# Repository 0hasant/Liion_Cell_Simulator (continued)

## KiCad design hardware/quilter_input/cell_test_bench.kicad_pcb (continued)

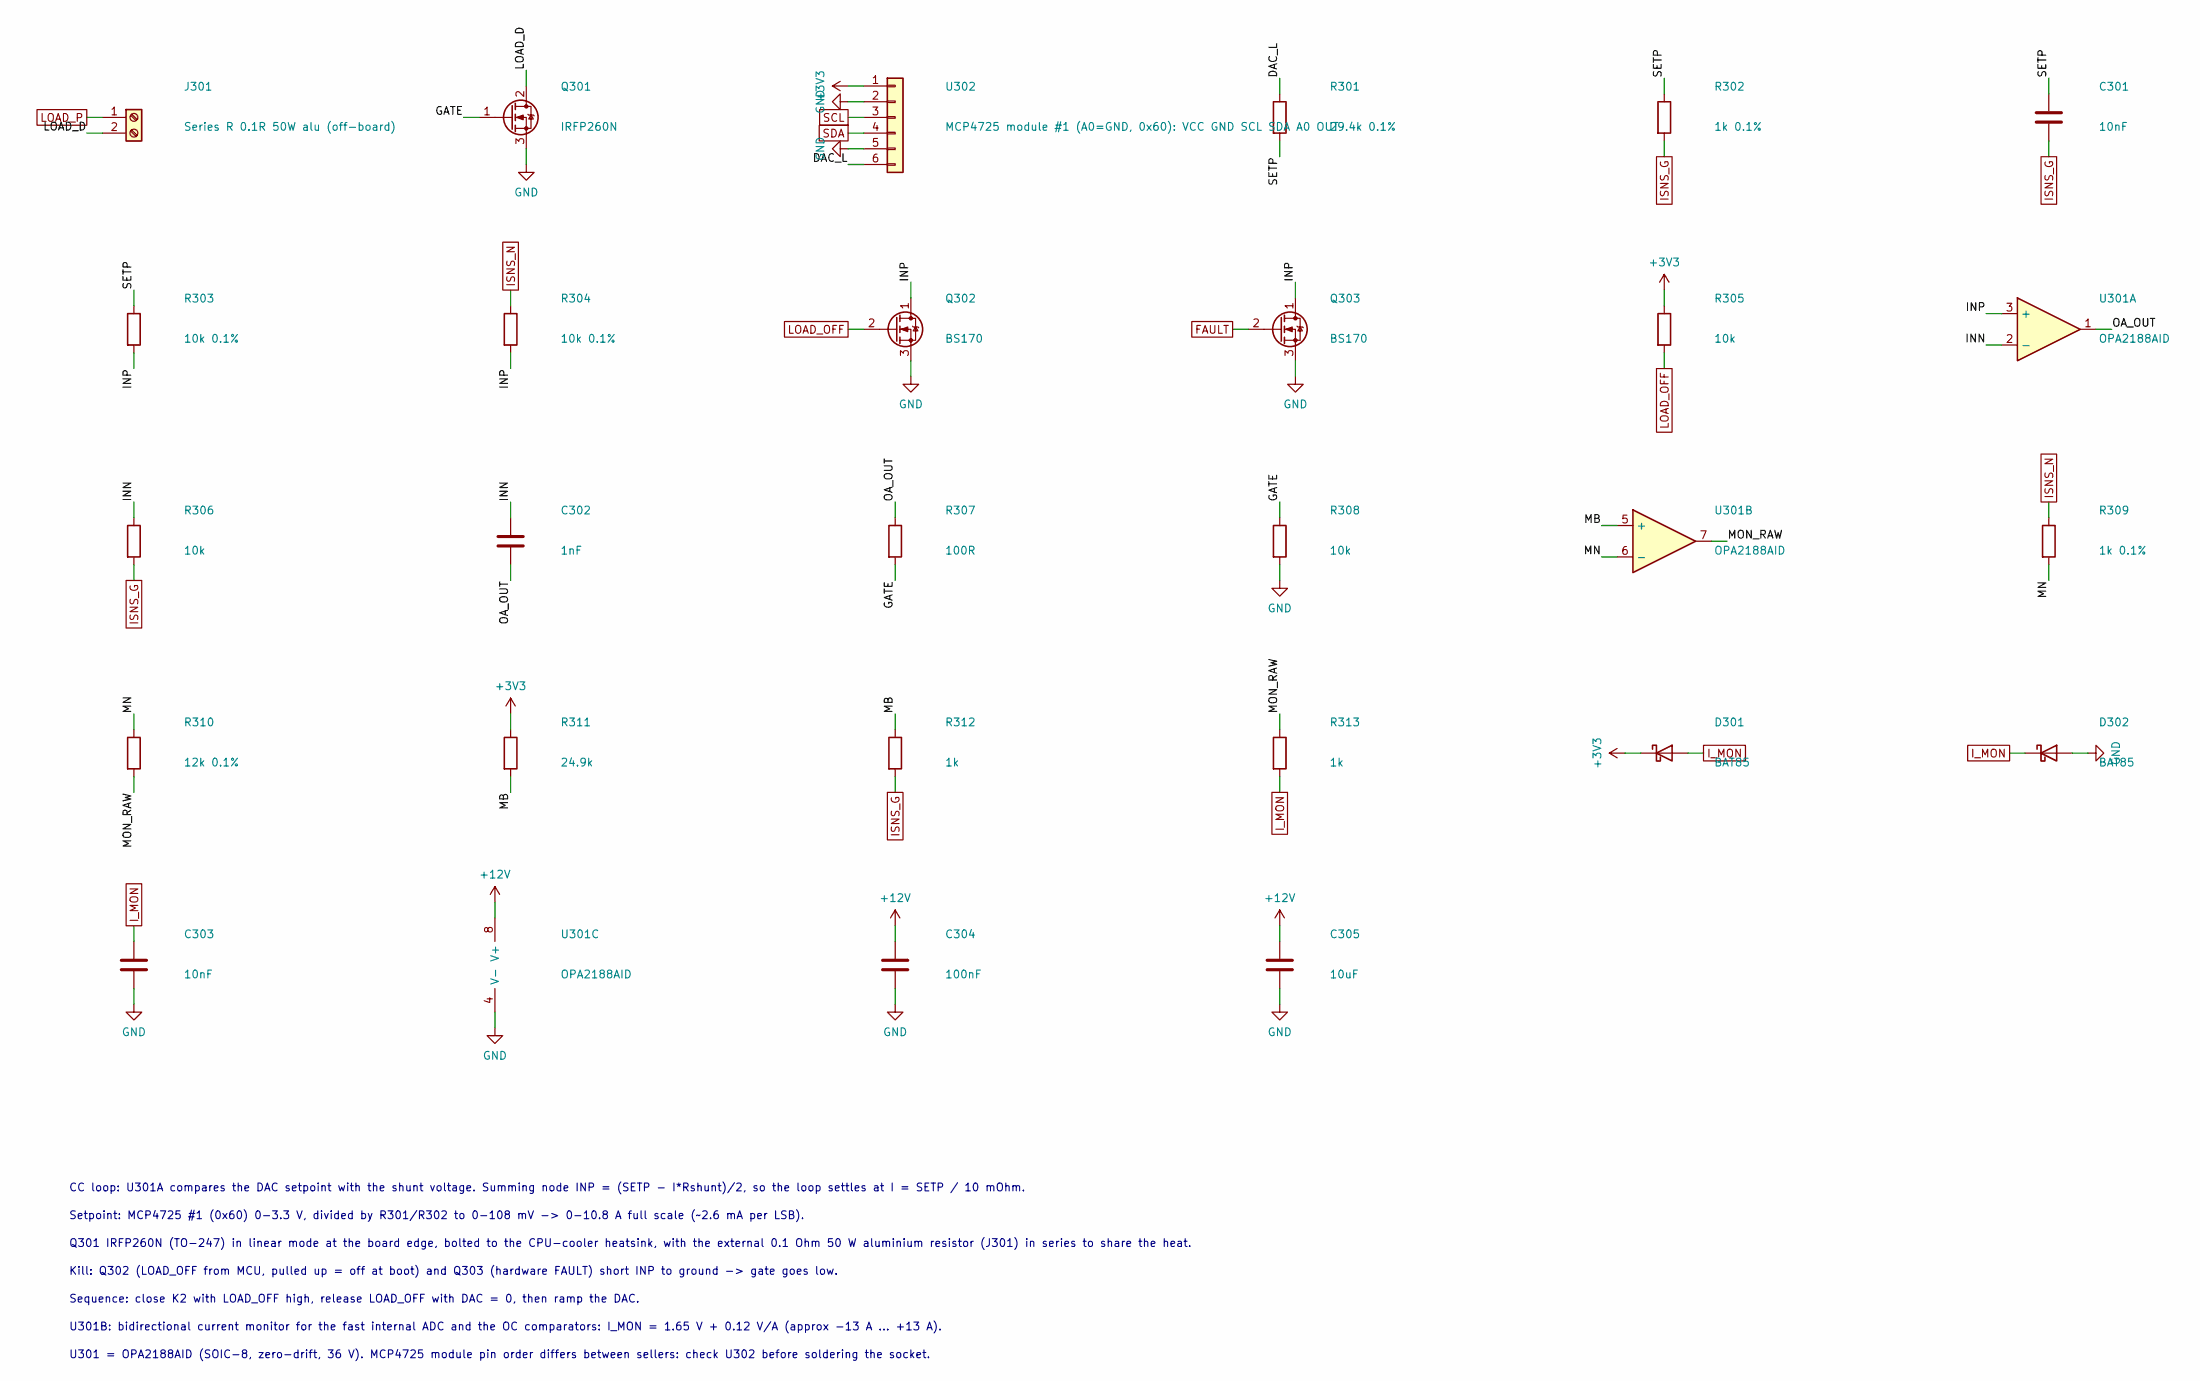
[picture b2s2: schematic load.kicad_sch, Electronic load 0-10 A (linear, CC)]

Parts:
C301, C303: 10nF; C_1206_3216Metric
C302: 1nF; C_1206_3216Metric
C304: 100nF; C_1206_3216Metric
C305: 10uF; C_1206_3216Metric
D301, D302: BAT85; D_DO-35_SOD27_P7.62mm_Horizontal; MPN BAT85,113
J301: Series R 0.1R 50W alu (off-board); TerminalBlock_Phoenix_MKDS-3-2-5.08_1x02_P5.08mm_Horizontal
Q301: IRFP260N; TO-247-3_Vertical; MPN IRFP260NPBF
Q302, Q303: BS170; TO-92_Inline_Wide; MPN BS170
R301: 29.4k 0.1%; R_1206_3216Metric
R302, R309: 1k 0.1%; R_1206_3216Metric
R303, R304: 10k 0.1%; R_1206_3216Metric
R305, R306, R308: 10k; R_1206_3216Metric
R307: 100R; R_1206_3216Metric
R310: 12k 0.1%; R_1206_3216Metric
R311: 24.9k; R_1206_3216Metric
R312, R313: 1k; R_1206_3216Metric
U301: OPA2188AID; SOIC-8_3.9x4.9mm_P1.27mm; MPN OPA2188AID
U302: MCP4725 module #1 (A0=GND, 0x60): VCC GND SCL SDA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; PinSocket_1x06_P2.54mm_Vertical

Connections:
+3V3: D301.1 (K), R305.1, R311.1, U302.1; also elsewhere on the board
+12V: C304.1, C305.1, U301.8 (V+); also elsewhere on the board
/Electronic_Load/DAC_L: R301.1, U302.6
/Electronic_Load/GATE: Q301.1 (G), R307.2, R308.1
/Electronic_Load/INN: C302.1, R306.1, U301.2 (-)
/Electronic_Load/INP: Q302.1 (D), Q303.1 (D), R303.2, R304.2, U301.3 (+)
/Electronic_Load/LOAD_D: J301.2, Q301.2 (D)
/Electronic_Load/MB: R311.2, R312.1, U301.5 (+)
/Electronic_Load/MN: R309.2, R310.1, U301.6 (-)
/Electronic_Load/MON_RAW: R310.2, R313.1, U301.7
/Electronic_Load/OA_OUT: C302.2, R307.1, U301.1
/Electronic_Load/SETP: C301.1, R301.2, R302.1, R303.1
FAULT: Q303.2 (G); also elsewhere on the board
GND: C303.2, C304.2, C305.2, D302.2 (A), Q301.3 (S), Q302.3 (S), Q303.3 (S), R308.2, U301.4 (V-), U302.2, U302.5; also elsewhere on the board
ISNS_G: C301.2, R302.2, R306.2, R312.2; also elsewhere on the board
ISNS_N: R304.1, R309.1; also elsewhere on the board
I_MON: C303.1, D301.2 (A), D302.1 (K), R313.2; also elsewhere on the board
LOAD_OFF: Q302.2 (G), R305.2; also elsewhere on the board
LOAD_P: J301.1; also elsewhere on the board
SCL: U302.3; also elsewhere on the board
SDA: U302.4; also elsewhere on the board

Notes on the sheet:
CC loop: U301A compares the DAC setpoint with the shunt voltage. Summing node INP = (SETP - I*Rshunt)/2, so the loop settles at I = SETP / 10 mOhm.
Setpoint: MCP4725 #1 (0x60) 0-3.3 V, divided by R301/R302 to 0-108 mV -> 0-10.8 A full scale (~2.6 mA per LSB).
Q301 IRFP260N (TO-247) in linear mode at the board edge, bolted to the CPU-cooler heatsink, with the external 0.1 Ohm 50 W aluminium resistor (J301) in series to share the heat.
Kill: Q302 (LOAD_OFF from MCU, pulled up = off at boot) and Q303 (hardware FAULT) short INP to ground -> gate goes low.
Sequence: close K2 with LOAD_OFF high, release LOAD_OFF with DAC = 0, then ramp the DAC.
U301B: bidirectional current monitor for the fast internal ADC and the OC comparators: I_MON = 1.65 V + 0.12 V/A (approx -13 A ... +13 A).
U301 = OPA2188AID (SOIC-8, zero-drift, 36 V). MCP4725 module pin order differs between sellers: check U302 before soldering the socket.

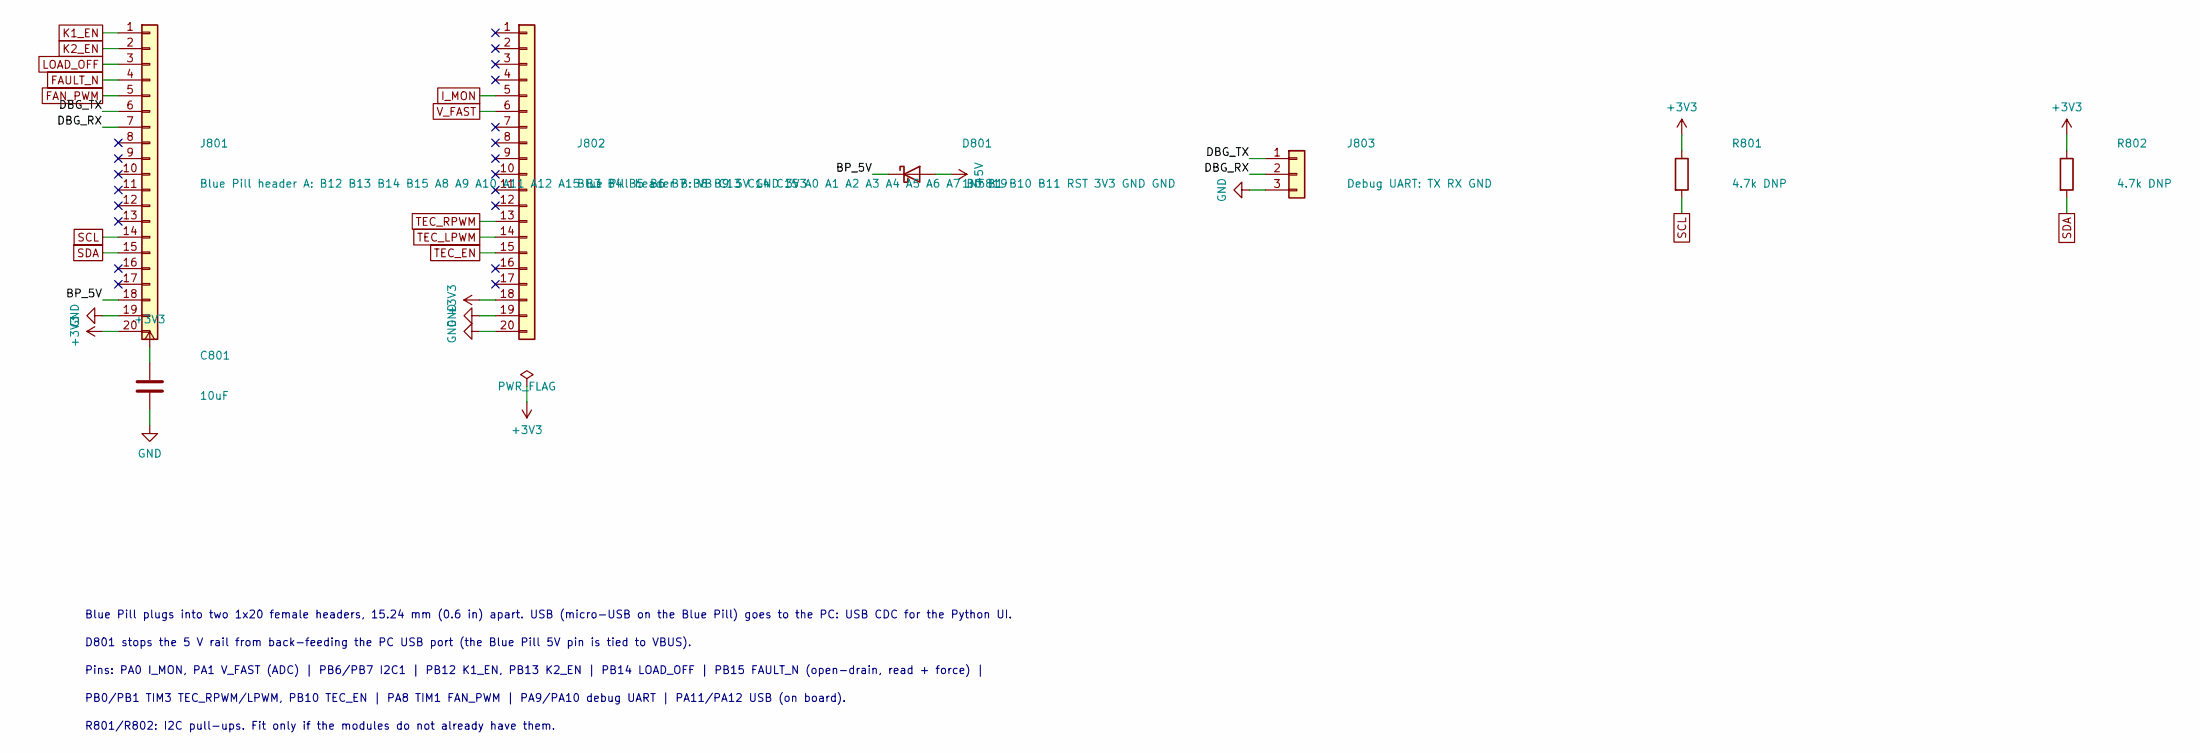
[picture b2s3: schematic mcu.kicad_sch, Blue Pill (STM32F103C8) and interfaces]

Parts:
C801: 10uF; C_1206_3216Metric
D801: 1N5819; D_DO-41_SOD81_P10.16mm_Horizontal; MPN 1N5819
J801: Blue Pill header A: B12 B13 B14 B15 A8 A9 A10 A11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; PinSocket_1x20_P2.54mm_Vertical
J802: Blue Pill header B: VB C13 C14 C15 A0 A1 A2 A3 A4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; PinSocket_1x20_P2.54mm_Vertical
J803: Debug UART: TX RX GND; PinHeader_1x03_P2.54mm_Vertical
R801, R802: 4.7k DNP; R_1206_3216Metric

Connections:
+3V3: C801.1, J801.20, J802.18, R801.1, R802.1; also elsewhere on the board
+5V: D801.2 (A); also elsewhere on the board
/MCU/BP_5V: D801.1 (K), J801.18
/MCU/DBG_RX: J801.7, J803.2
/MCU/DBG_TX: J801.6, J803.1
FAN_PWM: J801.5; also elsewhere on the board
FAULT_N: J801.4; also elsewhere on the board
GND: C801.2, J801.19, J802.19, J802.20, J803.3; also elsewhere on the board
I_MON: J802.5; also elsewhere on the board
K1_EN: J801.1; also elsewhere on the board
K2_EN: J801.2; also elsewhere on the board
LOAD_OFF: J801.3; also elsewhere on the board
SCL: J801.14, R801.2; also elsewhere on the board
SDA: J801.15, R802.2; also elsewhere on the board
TEC_EN: J802.15; also elsewhere on the board
TEC_LPWM: J802.14; also elsewhere on the board
TEC_RPWM: J802.13; also elsewhere on the board
V_FAST: J802.6; also elsewhere on the board

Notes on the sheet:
Blue Pill plugs into two 1x20 female headers, 15.24 mm (0.6 in) apart. USB (micro-USB on the Blue Pill) goes to the PC: USB CDC for the Python UI.
D801 stops the 5 V rail from back-feeding the PC USB port (the Blue Pill 5V pin is tied to VBUS).
Pins: PA0 I_MON, PA1 V_FAST (ADC) | PB6/PB7 I2C1 | PB12 K1_EN, PB13 K2_EN | PB14 LOAD_OFF | PB15 FAULT_N (open-drain, read + force) |
PB0/PB1 TIM3 TEC_RPWM/LPWM, PB10 TEC_EN | PA8 TIM1 FAN_PWM | PA9/PA10 debug UART | PA11/PA12 USB (on board).
R801/R802: I2C pull-ups. Fit only if the modules do not already have them.

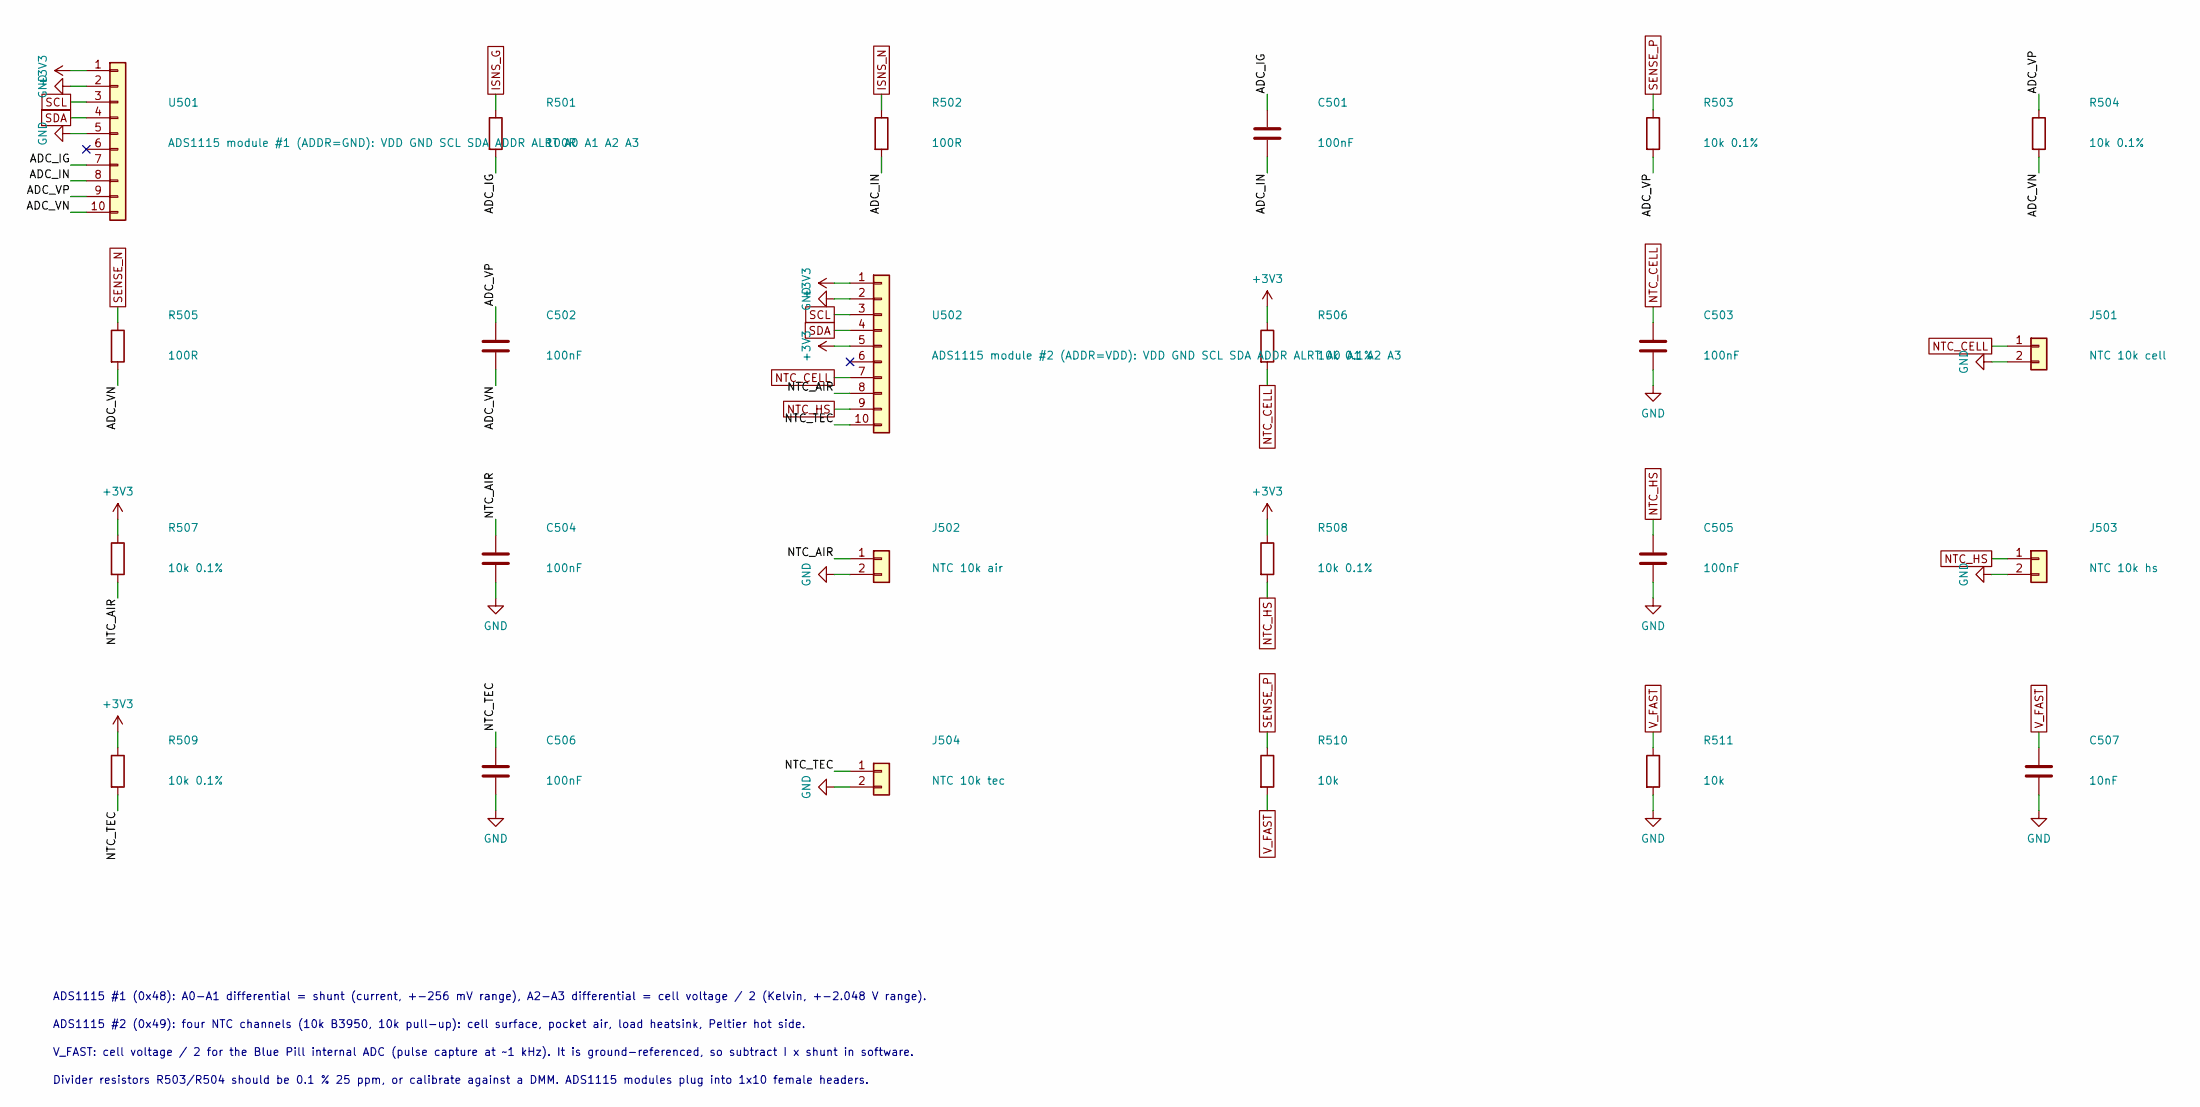
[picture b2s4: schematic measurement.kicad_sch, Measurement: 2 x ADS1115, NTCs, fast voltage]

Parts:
C501, C502, C503, C504, C505, C506: 100nF; C_1206_3216Metric
C507: 10nF; C_1206_3216Metric
J501: NTC 10k cell; JST_XH_B2B-XH-A_1x02_P2.50mm_Vertical
J502: NTC 10k air; JST_XH_B2B-XH-A_1x02_P2.50mm_Vertical
J503: NTC 10k hs; JST_XH_B2B-XH-A_1x02_P2.50mm_Vertical
J504: NTC 10k tec; JST_XH_B2B-XH-A_1x02_P2.50mm_Vertical
R501, R502, R505: 100R; R_1206_3216Metric
R503, R504, R506, R507, R508, R509: 10k 0.1%; R_1206_3216Metric
R510, R511: 10k; R_1206_3216Metric
U501: ADS1115 module #1 (ADDR=GND): VDD GND SCL SDA ADD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; PinSocket_1x10_P2.54mm_Vertical
U502: ADS1115 module #2 (ADDR=VDD): VDD GND SCL SDA ADD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; PinSocket_1x10_P2.54mm_Vertical

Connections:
+3V3: R506.1, R507.1, R508.1, R509.1, U501.1, U502.1, U502.5; also elsewhere on the board
/Measurement/ADC_IG: C501.1, R501.2, U501.7
/Measurement/ADC_IN: C501.2, R502.2, U501.8
/Measurement/ADC_VN: C502.2, R504.2, R505.2, U501.10
/Measurement/ADC_VP: C502.1, R503.2, R504.1, U501.9
/Measurement/NTC_AIR: C504.1, J502.1, R507.2, U502.8
/Measurement/NTC_TEC: C506.1, J504.1, R509.2, U502.10
GND: C503.2, C504.2, C505.2, C506.2, C507.2, J501.2, J502.2, J503.2, J504.2, R511.2, U501.2, U501.5, U502.2; also elsewhere on the board
ISNS_G: R501.1; also elsewhere on the board
ISNS_N: R502.1; also elsewhere on the board
NTC_CELL: C503.1, J501.1, R506.2, U502.7; also elsewhere on the board
NTC_HS: C505.1, J503.1, R508.2, U502.9; also elsewhere on the board
SCL: U501.3, U502.3; also elsewhere on the board
SDA: U501.4, U502.4; also elsewhere on the board
SENSE_N: R505.1; also elsewhere on the board
SENSE_P: R503.1, R510.1; also elsewhere on the board
V_FAST: C507.1, R510.2, R511.1; also elsewhere on the board

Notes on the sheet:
ADS1115 #1 (0x48): A0-A1 differential = shunt (current, +-256 mV range), A2-A3 differential = cell voltage / 2 (Kelvin, +-2.048 V range).
ADS1115 #2 (0x49): four NTC channels (10k B3950, 10k pull-up): cell surface, pocket air, load heatsink, Peltier hot side.
V_FAST: cell voltage / 2 for the Blue Pill internal ADC (pulse capture at ~1 kHz). It is ground-referenced, so subtract I x shunt in software.
Divider resistors R503/R504 should be 0.1 % 25 ppm, or calibrate against a DMM. ADS1115 modules plug into 1x10 female headers.

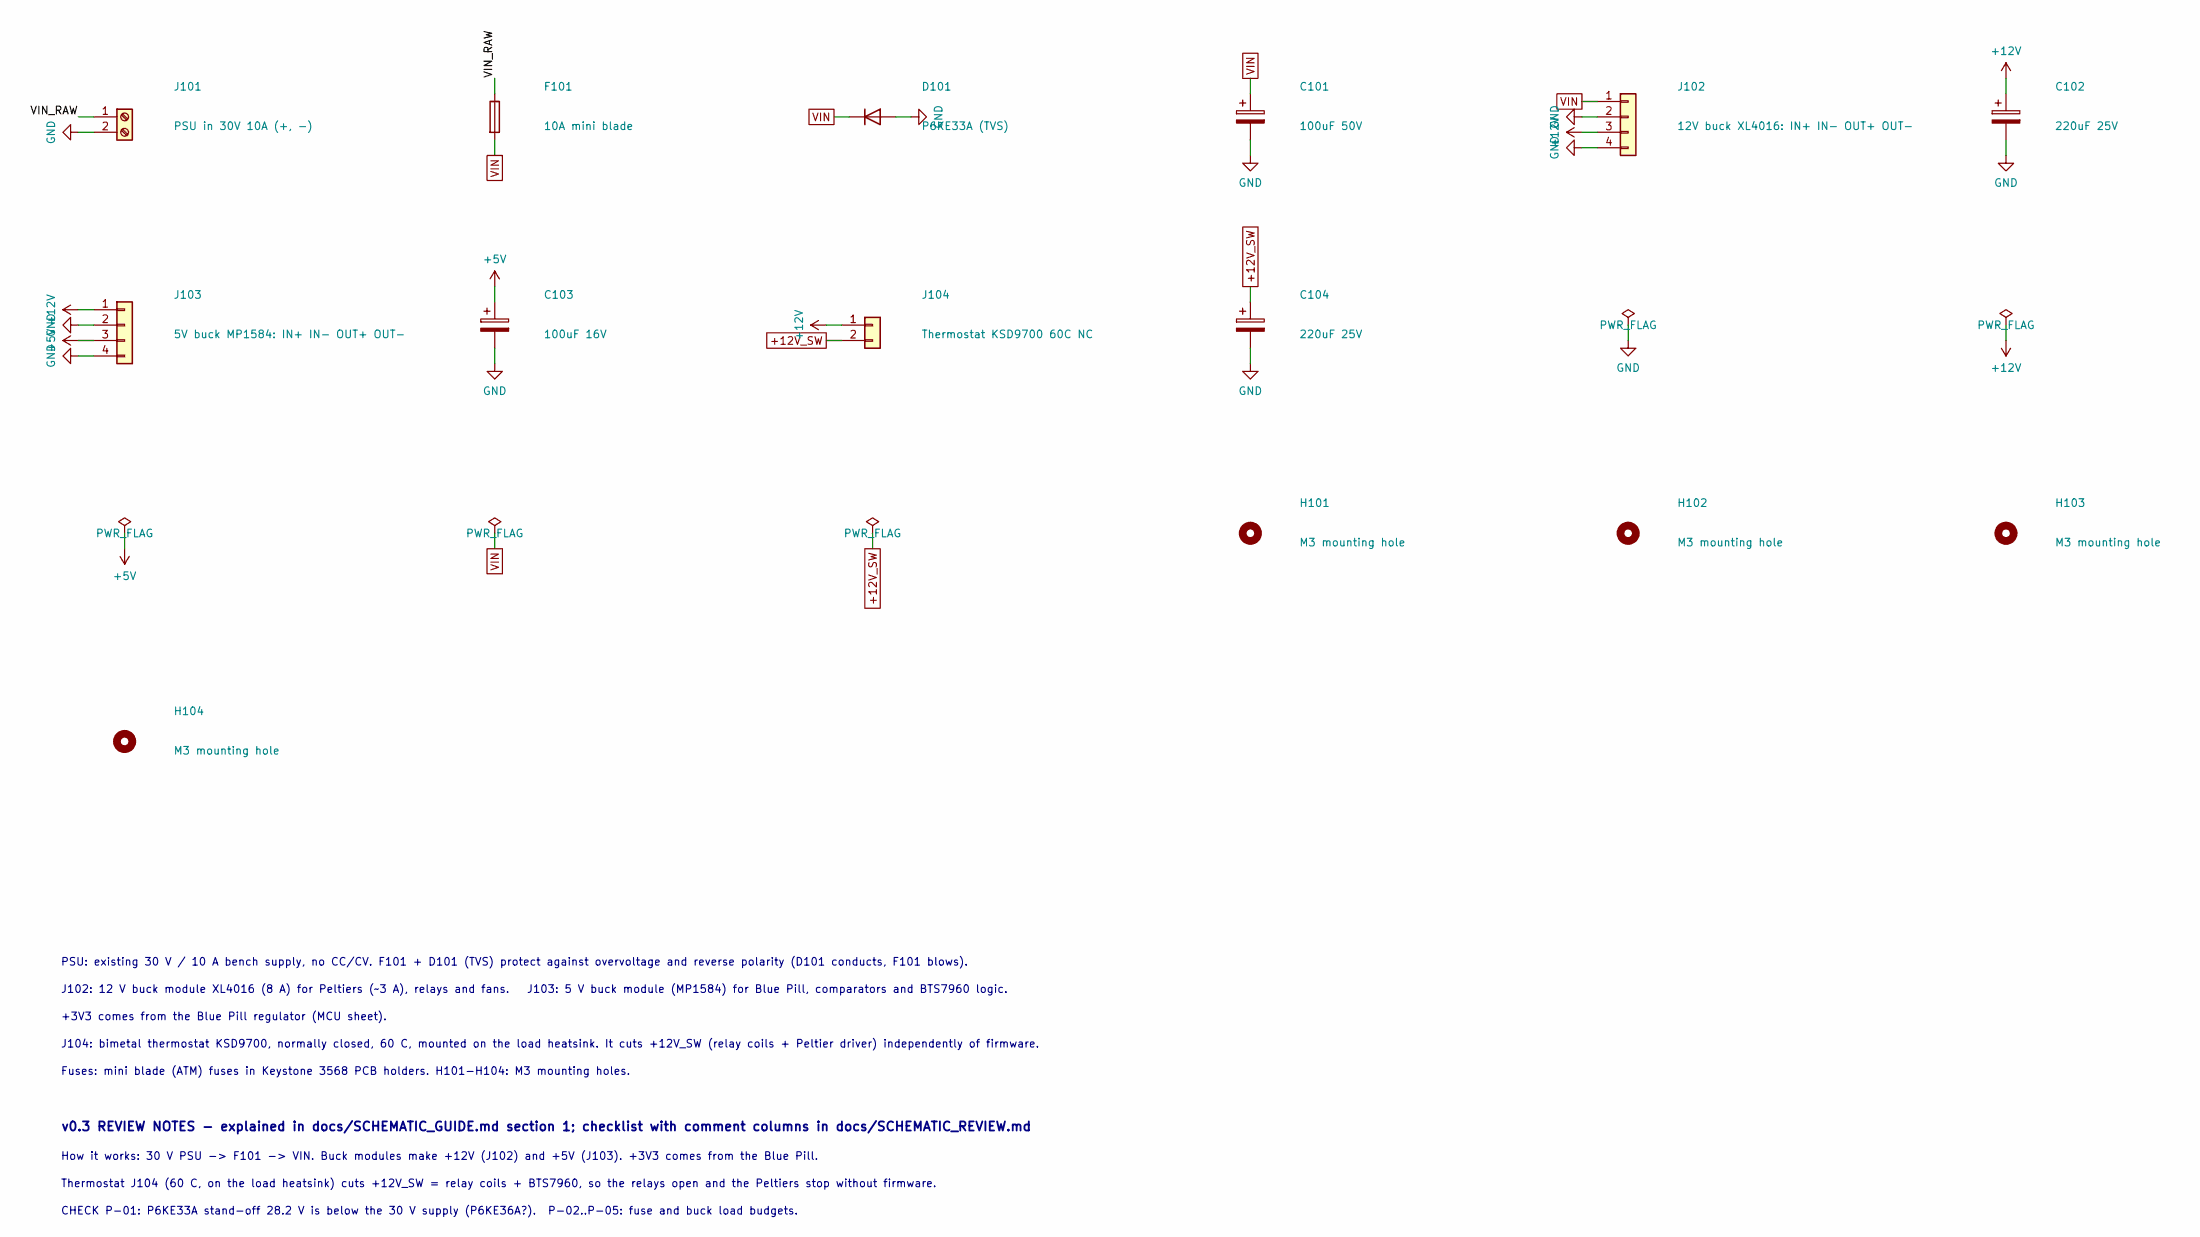
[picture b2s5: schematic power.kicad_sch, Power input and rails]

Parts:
C101: 100uF 50V; CP_Radial_D10.0mm_P5.00mm
C102, C104: 220uF 25V; CP_Radial_D8.0mm_P3.50mm
C103: 100uF 16V; CP_Radial_D6.3mm_P2.50mm
D101: P6KE33A (TVS); D_DO-15_P10.16mm_Horizontal; MPN P6KE33A
F101: 10A mini blade; Fuseholder_Blade_Mini_Keystone_3568; MPN Keystone 3568
H101, H102, H103, H104: M3 mounting hole; MountingHole_3.2mm_M3
J101: PSU in 30V 10A (+, -); TerminalBlock_Phoenix_MKDS-3-2-5.08_1x02_P5.08mm_Horizontal
J102: 12V buck XL4016: IN+ IN- OUT+ OUT-; TerminalBlock_Phoenix_MKDS-1,5-4-5.08_1x04_P5.08mm_Horizont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
J103: 5V buck MP1584: IN+ IN- OUT+ OUT-; TerminalBlock_Phoenix_MKDS-1,5-4-5.08_1x04_P5.08mm_Horizont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
J104: Thermostat KSD9700 60C NC; TerminalBlock_Phoenix_MKDS-1,5-2-5.08_1x02_P5.08mm_Horizont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

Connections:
+5V: C103.1, J103.3; also elsewhere on the board
+12V: C102.1, J102.3, J103.1, J104.1; also elsewhere on the board
+12V_SW: C104.1, J104.2; also elsewhere on the board
/Power/VIN_RAW: F101.1, J101.1
GND: C101.2, C102.2, C103.2, C104.2, D101.2 (A), J101.2, J102.2, J102.4, J103.2, J103.4; also elsewhere on the board
VIN: C101.1, D101.1 (K), F101.2, J102.1; also elsewhere on the board

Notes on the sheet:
PSU: existing 30 V / 10 A bench supply, no CC/CV. F101 + D101 (TVS) protect against overvoltage and reverse polarity (D101 conducts, F101 blows).
J102: 12 V buck module XL4016 (8 A) for Peltiers (~3 A), relays and fans. J103: 5 V buck module (MP1584) for Blue Pill, comparators and BTS7960 logic.
+3V3 comes from the Blue Pill regulator (MCU sheet).
J104: bimetal thermostat KSD9700, normally closed, 60 C, mounted on the load heatsink. It cuts +12V_SW (relay coils + Peltier driver) independently of firmware.
Fuses: mini blade (ATM) fuses in Keystone 3568 PCB holders. H101-H104: M3 mounting holes.
v0.3 REVIEW NOTES - explained in docs/SCHEMATIC_GUIDE.md section 1; checklist with comment columns in docs/SCHEMATIC_REVIEW.md
How it works: 30 V PSU -> F101 -> VIN. Buck modules make +12V (J102) and +5V (J103). +3V3 comes from the Blue Pill.
Thermostat J104 (60 C, on the load heatsink) cuts +12V_SW = relay coils + BTS7960, so the relays open and the Peltiers stop without firmware.
CHECK P-01: P6KE33A stand-off 28.2 V is below the 30 V supply (P6KE36A?). P-02..P-05: fuse and buck load budgets.

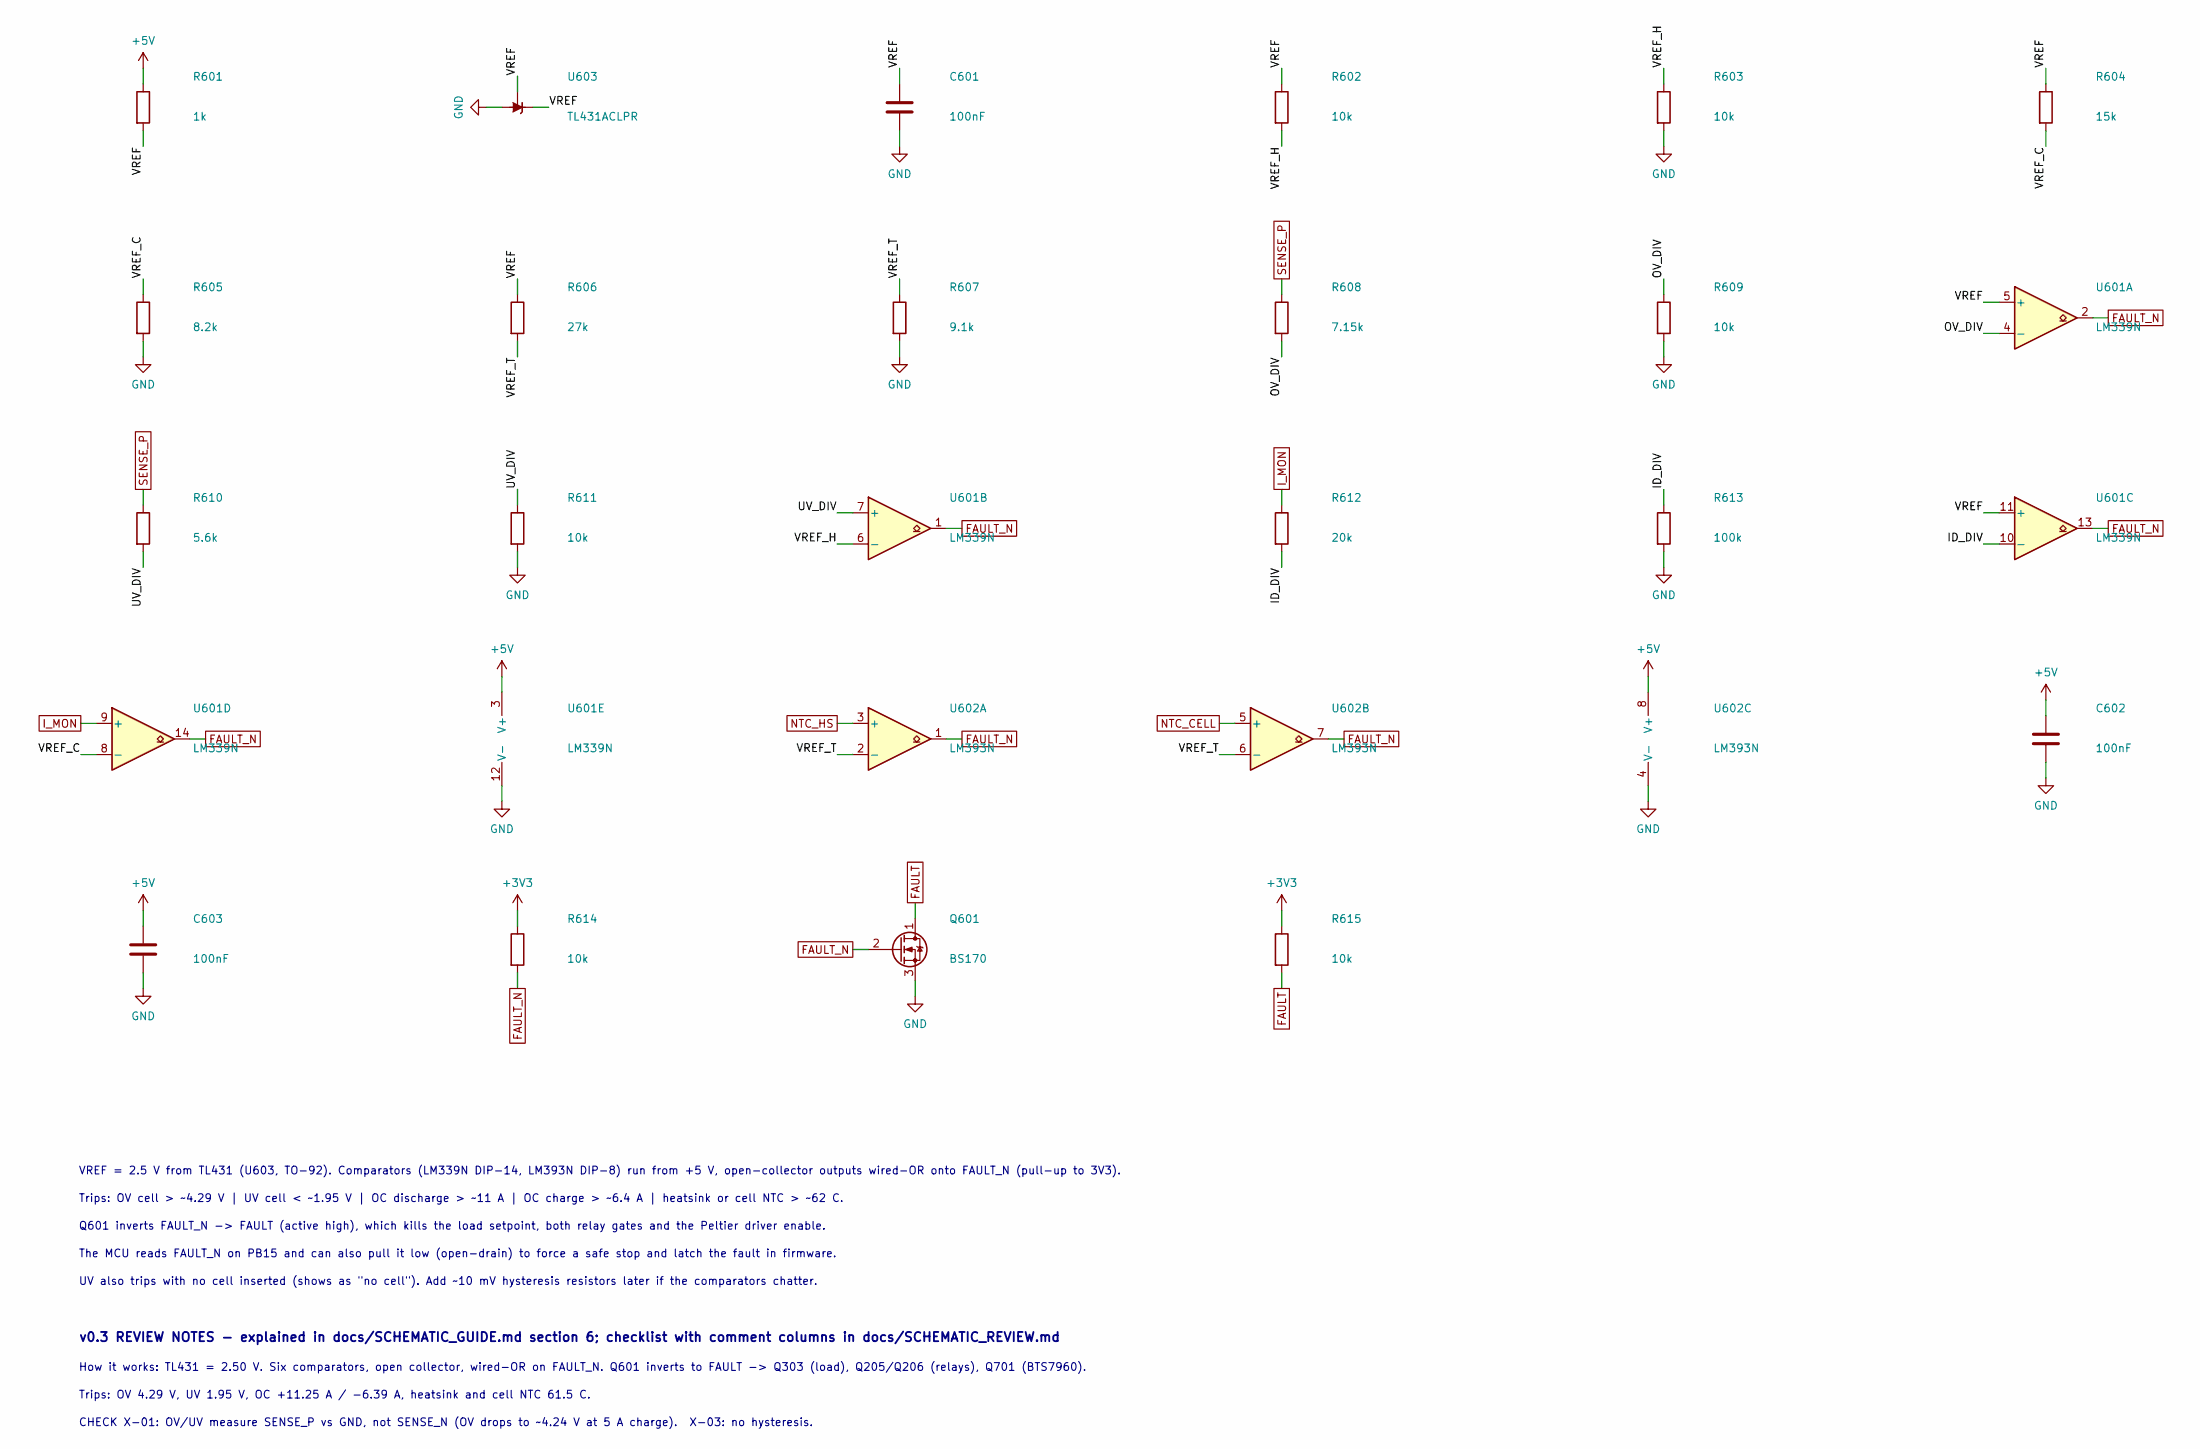
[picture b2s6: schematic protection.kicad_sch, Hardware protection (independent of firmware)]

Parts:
C601, C602, C603: 100nF; C_1206_3216Metric
Q601: BS170; TO-92_Inline_Wide; MPN BS170
R601: 1k; R_1206_3216Metric
R602, R603, R609, R611, R614, R615: 10k; R_1206_3216Metric
R604: 15k; R_1206_3216Metric
R605: 8.2k; R_1206_3216Metric
R606: 27k; R_1206_3216Metric
R607: 9.1k; R_1206_3216Metric
R608: 7.15k; R_1206_3216Metric
R610: 5.6k; R_1206_3216Metric
R612: 20k; R_1206_3216Metric
R613: 100k; R_1206_3216Metric
U601: LM339N; DIP-14_W7.62mm; MPN LM339N
U602: LM393N; DIP-8_W7.62mm; MPN LM393N
U603: TL431ACLPR; TO-92_Inline_Wide; MPN TL431ACLPR

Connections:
+3V3: R614.1, R615.1; also elsewhere on the board
+5V: C602.1, C603.1, R601.1, U601.3 (V+), U602.8 (V+); also elsewhere on the board
/Protection/ID_DIV: R612.2, R613.1, U601.10 (-)
/Protection/OV_DIV: R608.2, R609.1, U601.4 (-)
/Protection/UV_DIV: R610.2, R611.1, U601.7 (+)
/Protection/VREF: C601.1, R601.2, R602.1, R604.1, R606.1, U601.5 (+), U601.11 (+), U603.1 (REF), U603.3 (K)
/Protection/VREF_C: R604.2, R605.1, U601.8 (-)
/Protection/VREF_H: R602.2, R603.1, U601.6 (-)
/Protection/VREF_T: R606.2, R607.1, U602.2 (-), U602.6 (-)
FAULT: Q601.1 (D), R615.2; also elsewhere on the board
FAULT_N: Q601.2 (G), R614.2, U601.1, U601.2, U601.13, U601.14, U602.1, U602.7; also elsewhere on the board
GND: C601.2, C602.2, C603.2, Q601.3 (S), R603.2, R605.2, R607.2, R609.2, R611.2, R613.2, U601.12 (V-), U602.4 (V-), U603.2 (A); also elsewhere on the board
I_MON: R612.1, U601.9 (+); also elsewhere on the board
NTC_CELL: U602.5 (+); also elsewhere on the board
NTC_HS: U602.3 (+); also elsewhere on the board
SENSE_P: R608.1, R610.1; also elsewhere on the board

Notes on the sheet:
VREF = 2.5 V from TL431 (U603, TO-92). Comparators (LM339N DIP-14, LM393N DIP-8) run from +5 V, open-collector outputs wired-OR onto FAULT_N (pull-up to 3V3).
Trips: OV cell > ~4.29 V | UV cell < ~1.95 V | OC discharge > ~11 A | OC charge > ~6.4 A | heatsink or cell NTC > ~62 C.
Q601 inverts FAULT_N -> FAULT (active high), which kills the load setpoint, both relay gates and the Peltier driver enable.
The MCU reads FAULT_N on PB15 and can also pull it low (open-drain) to force a safe stop and latch the fault in firmware.
UV also trips with no cell inserted (shows as "no cell"). Add ~10 mV hysteresis resistors later if the comparators chatter.
v0.3 REVIEW NOTES - explained in docs/SCHEMATIC_GUIDE.md section 6; checklist with comment columns in docs/SCHEMATIC_REVIEW.md
How it works: TL431 = 2.50 V. Six comparators, open collector, wired-OR on FAULT_N. Q601 inverts to FAULT -> Q303 (load), Q205/Q206 (relays), Q701 (BTS7960).
Trips: OV 4.29 V, UV 1.95 V, OC +11.25 A / -6.39 A, heatsink and cell NTC 61.5 C.
CHECK X-01: OV/UV measure SENSE_P vs GND, not SENSE_N (OV drops to ~4.24 V at 5 A charge). X-03: no hysteresis.
